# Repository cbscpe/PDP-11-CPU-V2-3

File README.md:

# CPU Board for the PDP-11/Hack V2-3

## Introduction

The PDP-11/Hack is a home-brew PDP-11 compatible computer using eurocard sized
PCBs and DIN41612 bus connectors. The PDP-11/Hack uses it's own bus, named QBUS64,
which is heavily based on the real Q-BUS regarding timing and signalling. The major
difference is that the address/data bus uses non-inverted tri-state signal.

## CPU Card

After the first and so far only CPU card built in 2017 various ideas existed for a
new CPU card that fixes all the issues of the first CPU card and added additional
functions. Most notably the new CPU card has the following features

- DCJ11 processor running up to 22MHz
- 2 or 4 Mbyte of RAM, a PDP-11 can have a maximum of 4Mbyte
- power-up configuration with all 16 bits valid
- maintenance register with all 16 bits valid
- BootROM at the standard IO page addresses 173xxx<sub>8</sub> and 165xxx<sub>8</sub>
- Console using a DC319
- Additional SLU using a second DC319
- Line-time clock
- PDP-11/93,94 compatible advanced status register to read and write the DS1315 real-time clock

## Schematic

## Additional Information

For a full description of this and other projects related not only to PDP-11 
see my [Home Page](https://www.5volts.ch/). For a detailed description of the
CPU Card Version 2-3 see [PDP-11/Hack](https://www.5volts.ch/pages/pdp11hack/)

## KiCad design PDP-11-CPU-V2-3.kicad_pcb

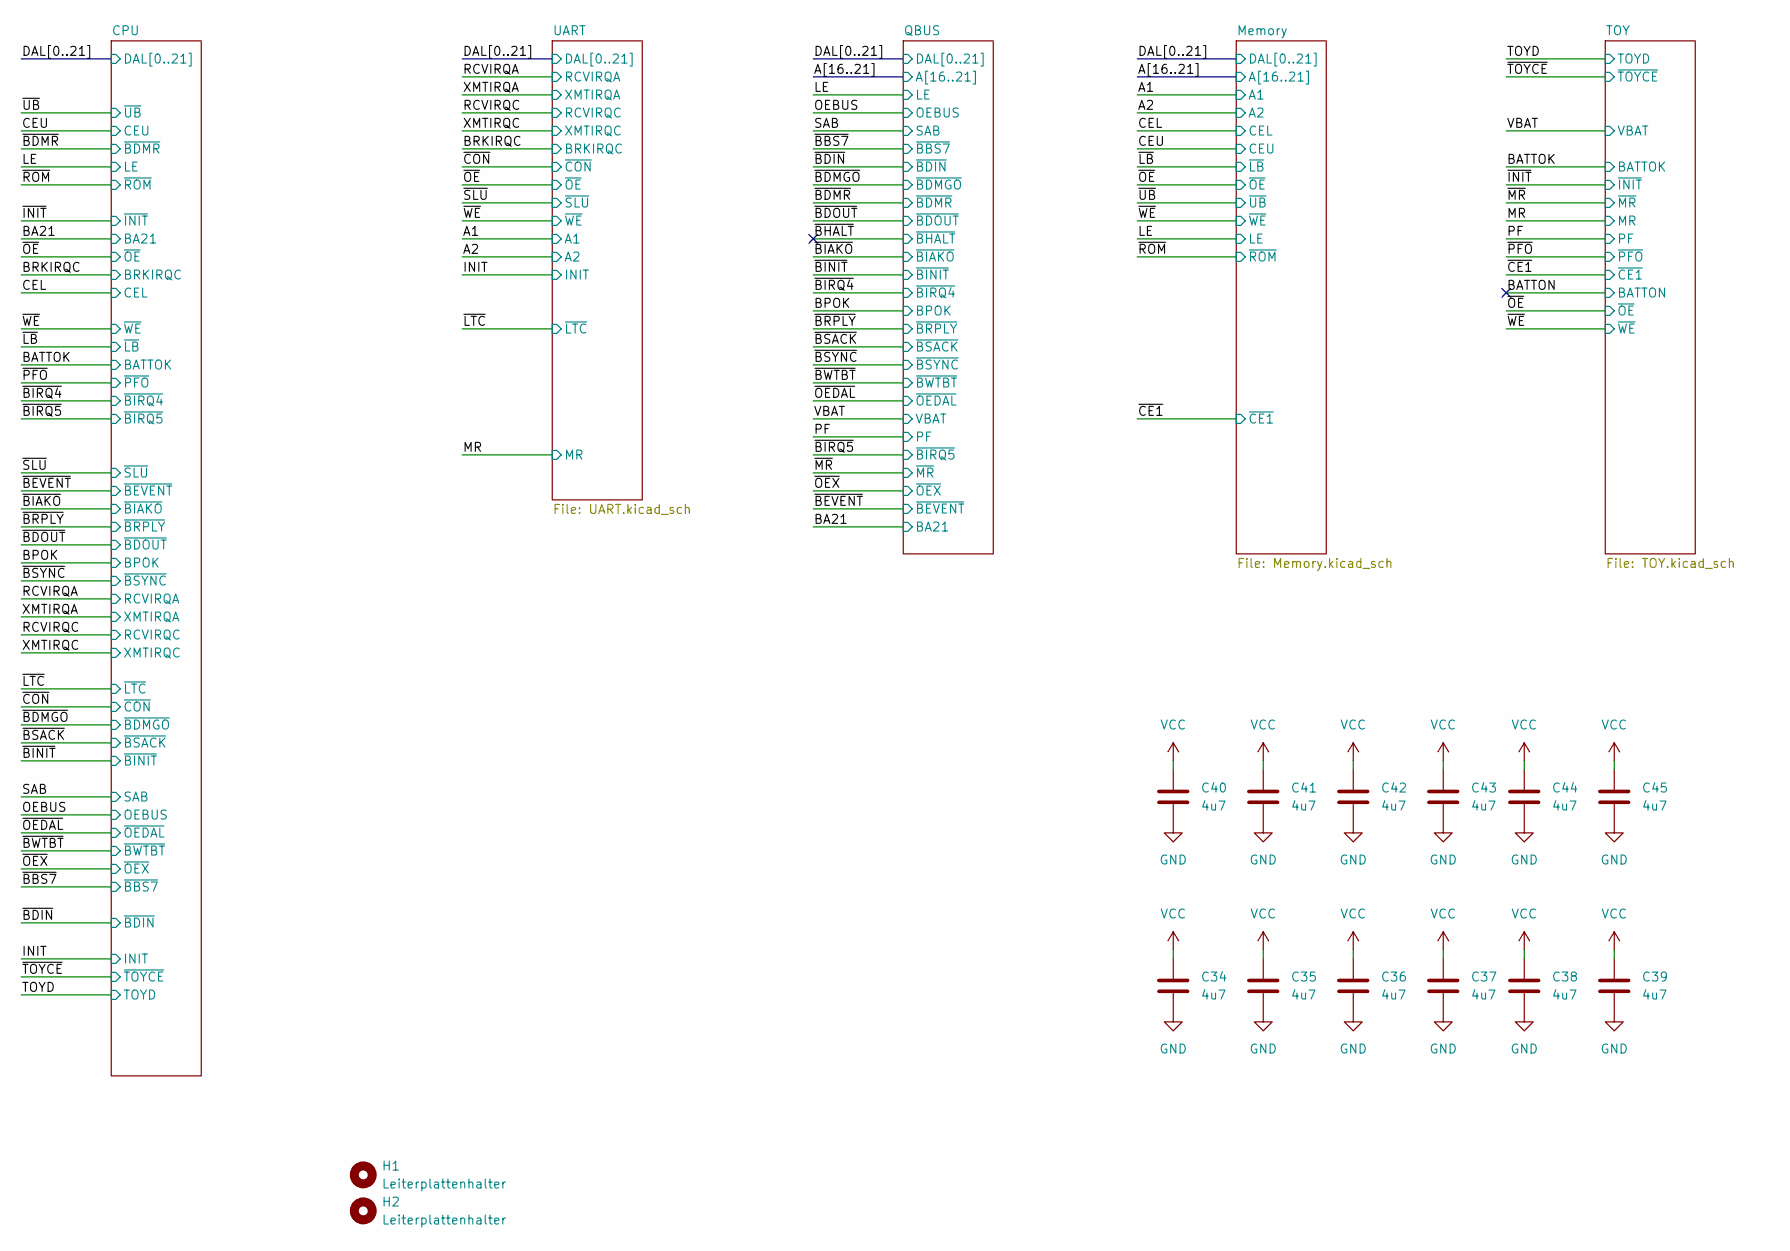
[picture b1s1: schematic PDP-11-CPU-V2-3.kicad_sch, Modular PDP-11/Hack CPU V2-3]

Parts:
C34, C35, C36, C37, C38, C39, C40, C41, C42, C43, C44, C45: 4u7; CP_EIA-3528-12_Kemet-T_HandSolder
H1, H2: Leiterplattenhalter; MountingHole_2.7mm_M2.5_DIN965

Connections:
GND: C34.2, C35.2, C36.2, C37.2, C38.2, C39.2, C40.2, C41.2, C42.2, C43.2, C44.2, C45.2; also elsewhere on the board
VCC: C34.1, C35.1, C36.1, C37.1, C38.1, C39.1, C40.1, C41.1, C42.1, C43.1, C44.1, C45.1; also elsewhere on the board

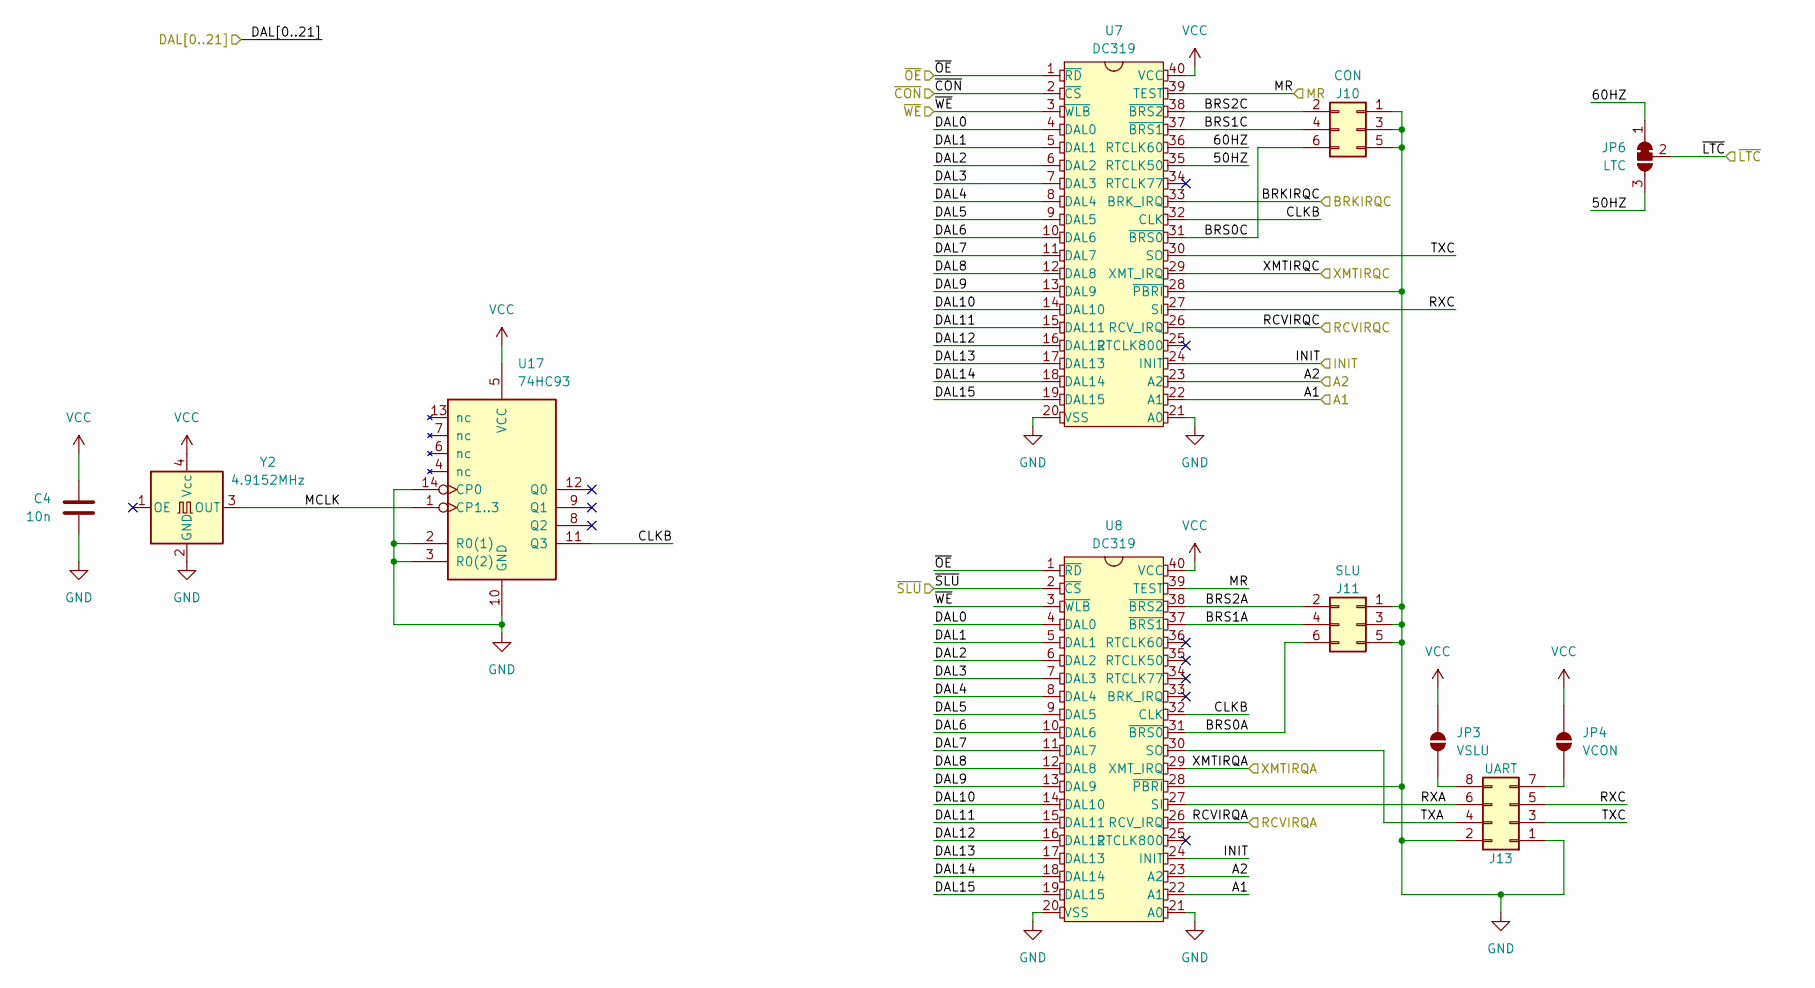
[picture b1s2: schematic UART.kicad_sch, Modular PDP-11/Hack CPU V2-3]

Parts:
C4: 10n; C_0603_1608Metric_Pad1.08x0.95mm_HandSolder
J10: CON; PinHeader_2x03_P2.54mm_Vertical
J11: SLU; PinHeader_2x03_P2.54mm_Vertical
J13: UART; PinHeader_2x04_P2.54mm_Horizontal
JP3: VSLU; SolderJumper-2_P1.3mm_Open_RoundedPad1.0x1.5mm
JP4: VCON; SolderJumper-2_P1.3mm_Open_RoundedPad1.0x1.5mm
JP6: LTC; SolderJumper-3_P1.3mm_Bridged12_RoundedPad1.0x1.5mm
U7, U8: DC319; DIP-40_W15.24mm_Socket
U17: 74HC93; SO-14_3.9x8.65mm_P1.27mm
Y2: 4.9152MHz; Oscillator_SMD_SeikoEpson_SG8002LB-4Pin_5.0x3.2mm_HandSolde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

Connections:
/A1: U7.22 (A1), U8.22 (A1); also elsewhere on the board
/A2: U7.23 (A2), U8.23 (A2); also elsewhere on the board
/BRKIRQC: U7.33 (BRK_IRQ); also elsewhere on the board
/DAL0: U7.4 (DAL0), U8.4 (DAL0); also elsewhere on the board
/DAL1: U7.5 (DAL1), U8.5 (DAL1); also elsewhere on the board
/DAL2: U7.6 (DAL2), U8.6 (DAL2); also elsewhere on the board
/DAL3: U7.7 (DAL3), U8.7 (DAL3); also elsewhere on the board
/DAL4: U7.8 (DAL4), U8.8 (DAL4); also elsewhere on the board
/DAL5: U7.9 (DAL5), U8.9 (DAL5); also elsewhere on the board
/DAL6: U7.10 (DAL6), U8.10 (DAL6); also elsewhere on the board
/DAL7: U7.11 (DAL7), U8.11 (DAL7); also elsewhere on the board
/DAL8: U7.12 (DAL8), U8.12 (DAL8); also elsewhere on the board
/DAL9: U7.13 (DAL9), U8.13 (DAL9); also elsewhere on the board
/DAL10: U7.14 (DAL10), U8.14 (DAL10); also elsewhere on the board
/DAL11: U7.15 (DAL11), U8.15 (DAL11); also elsewhere on the board
/DAL12: U7.16 (DAL12), U8.16 (DAL12); also elsewhere on the board
/DAL13: U7.17 (DAL13), U8.17 (DAL13); also elsewhere on the board
/DAL14: U7.18 (DAL14), U8.18 (DAL14); also elsewhere on the board
/DAL15: U7.19 (DAL15), U8.19 (DAL15); also elsewhere on the board
/INIT: U7.24 (INIT), U8.24 (INIT); also elsewhere on the board
/MR: U7.39 (TEST), U8.39 (TEST); also elsewhere on the board
/RCVIRQA: U8.26 (RCV_IRQ); also elsewhere on the board
/RCVIRQC: U7.26 (RCV_IRQ); also elsewhere on the board
/UART/50HZ: JP6.3 (B), U7.35 (RTCLK50)
/UART/60HZ: JP6.1 (A), U7.36 (RTCLK60)
/UART/BRS0A: J11.6, U8.31 (~BRS0)
/UART/BRS0C: J10.6, U7.31 (~BRS0)
/UART/BRS1A: J11.4, U8.37 (~BRS1)
/UART/BRS1C: J10.4, U7.37 (~BRS1)
/UART/BRS2A: J11.2, U8.38 (~BRS2)
/UART/BRS2C: J10.2, U7.38 (~BRS2)
/UART/CLKB: U7.32 (CLK), U8.32 (CLK), U17.11 (Q3)
/UART/MCLK: U17.1 (CP1..3), Y2.3 (OUT)
/UART/RXA: J13.6, U8.27 (SI)
/UART/RXC: J13.5, U7.27 (SI)
/UART/TXA: J13.4, U8.30 (SO)
/UART/TXC: J13.3, U7.30 (SO)
/XMTIRQA: U8.29 (XMT_IRQ); also elsewhere on the board
/XMTIRQC: U7.29 (XMT_IRQ); also elsewhere on the board
/~CON: U7.2 (~CS); also elsewhere on the board
/~LTC: JP6.2 (C); also elsewhere on the board
/~OE: U7.1 (~RD), U8.1 (~RD); also elsewhere on the board
/~SLU: U8.2 (~CS); also elsewhere on the board
/~WE: U7.3 (~WLB), U8.3 (~WLB); also elsewhere on the board
GND: C4.2, J10.1, J10.3, J10.5, J11.1, J11.3, J11.5, J13.1, J13.2, U7.20 (VSS), U7.21 (A0), U7.28 (~PBRI), U8.20 (VSS), U8.21 (A0), U8.28 (~PBRI), U17.2 (R0(1)), U17.3 (R0(2)), U17.10 (GND), U17.14 (CP0), Y2.2 (GND); also elsewhere on the board
unnamed: J13.7, JP4.1 (A)
unnamed: J13.8, JP3.1 (A)
VCC: C4.1, JP3.2 (B), JP4.2 (B), U7.40 (VCC), U8.40 (VCC), U17.5 (VCC), Y2.4 (Vcc); also elsewhere on the board

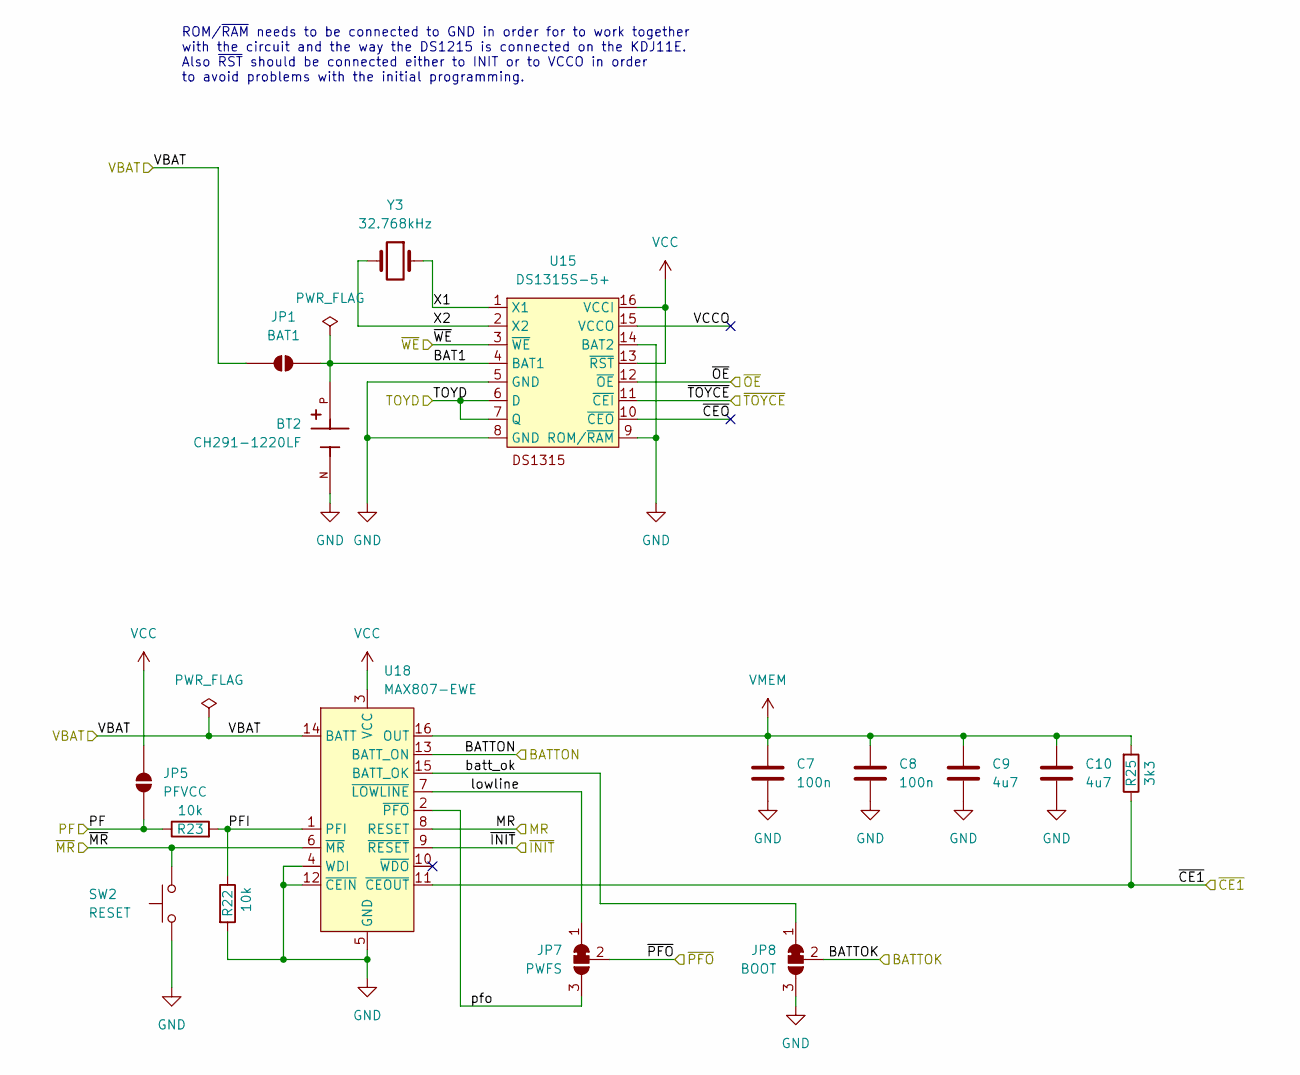
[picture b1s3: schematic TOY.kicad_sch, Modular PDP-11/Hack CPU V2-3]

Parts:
BT2: CH291-1220LF; BAT_CH291-1220LF
C7, C8: 100n; C_0603_1608Metric_Pad1.08x0.95mm_HandSolder
C9, C10: 4u7; CP_EIA-3528-12_Kemet-T_HandSolder
JP1: BAT1; SolderJumper-2_P1.3mm_Open_RoundedPad1.0x1.5mm
JP5: PFVCC; SolderJumper-2_P1.3mm_Open_RoundedPad1.0x1.5mm
JP7: PWFS; SolderJumper-3_P1.3mm_Bridged12_RoundedPad1.0x1.5mm
JP8: BOOT; SolderJumper-3_P1.3mm_Bridged12_RoundedPad1.0x1.5mm
R22, R23: 10k; R_0603_1608Metric_Pad0.98x0.95mm_HandSolder
R25: 3k3; R_0603_1608Metric_Pad0.98x0.95mm_HandSolder
SW2: RESET; SW_PUSH_6mm
U15: DS1315S-5+; SOIC-16W_7.5x10.3mm_P1.27mm
U18: MAX807-EWE; SOIC-16W_7.5x10.3mm_P1.27mm
Y3: 32.768kHz; Crystal_SMD_EuroQuartz_EQ161-2Pin_3.2x1.5mm_HandSoldering

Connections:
/BATTOK: JP8.2 (C); also elsewhere on the board
/BATTON: U18.13 (BATT_ON)
/MR: U18.8 (RESET); also elsewhere on the board
/PF: JP5.2 (B), R23.1; also elsewhere on the board
/TOY/BAT1: BT2.P, JP1.1 (A), U15.4 (BAT1)
/TOY/PFI: R22.1, R23.2, U18.1 (PFI)
/TOY/VCCO: U15.15 (VCCO)
/TOY/X1: U15.1 (X1), Y3.1
/TOY/X2: U15.2 (X2), Y3.2
/TOY/batt_ok: JP8.1 (A), U18.15 (BATT_OK)
/TOY/lowline: JP7.1 (A), U18.7 (~LOWLINE)
/TOY/pfo: JP7.3 (B), U18.2 (~PFO)
/TOY/~CEO: U15.10 (~CEO)
/TOYD: U15.6 (D), U15.7 (Q); also elsewhere on the board
/VBAT: JP1.2 (B), U18.14 (BATT); also elsewhere on the board
/~CE1: R25.1, U18.11 (~CEOUT); also elsewhere on the board
/~INIT: U18.9 (~RESET); also elsewhere on the board
/~MR: SW2.2, U18.6 (~MR); also elsewhere on the board
/~OE: U15.12 (~OE); also elsewhere on the board
/~PFO: JP7.2 (C); also elsewhere on the board
/~TOYCE: U15.11 (~CEI); also elsewhere on the board
/~WE: U15.3 (~WE); also elsewhere on the board
GND: BT2.N, C7.2, C8.2, C9.2, C10.2, JP8.3 (B), R22.2, SW2.1, U15.5 (GND), U15.8 (GND), U15.9 (ROM/~RAM), U15.14 (BAT2), U18.4 (WDI), U18.5 (GND), U18.12 (~CEIN); also elsewhere on the board
VCC: JP5.1 (A), U15.13 (~RST), U15.16 (VCCI), U18.3 (VCC); also elsewhere on the board
VMEM: C7.1, C8.1, C9.1, C10.1, R25.2, U18.16 (OUT); also elsewhere on the board

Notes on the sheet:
ROM/~{RAM} needs to be connected to GND in order for to work together with the circuit and the way the DS1215 is connected on the KDJ11E. Also ~{RST} should be connected either to INIT or to VCCO in order to avoid problems with the initial programming.

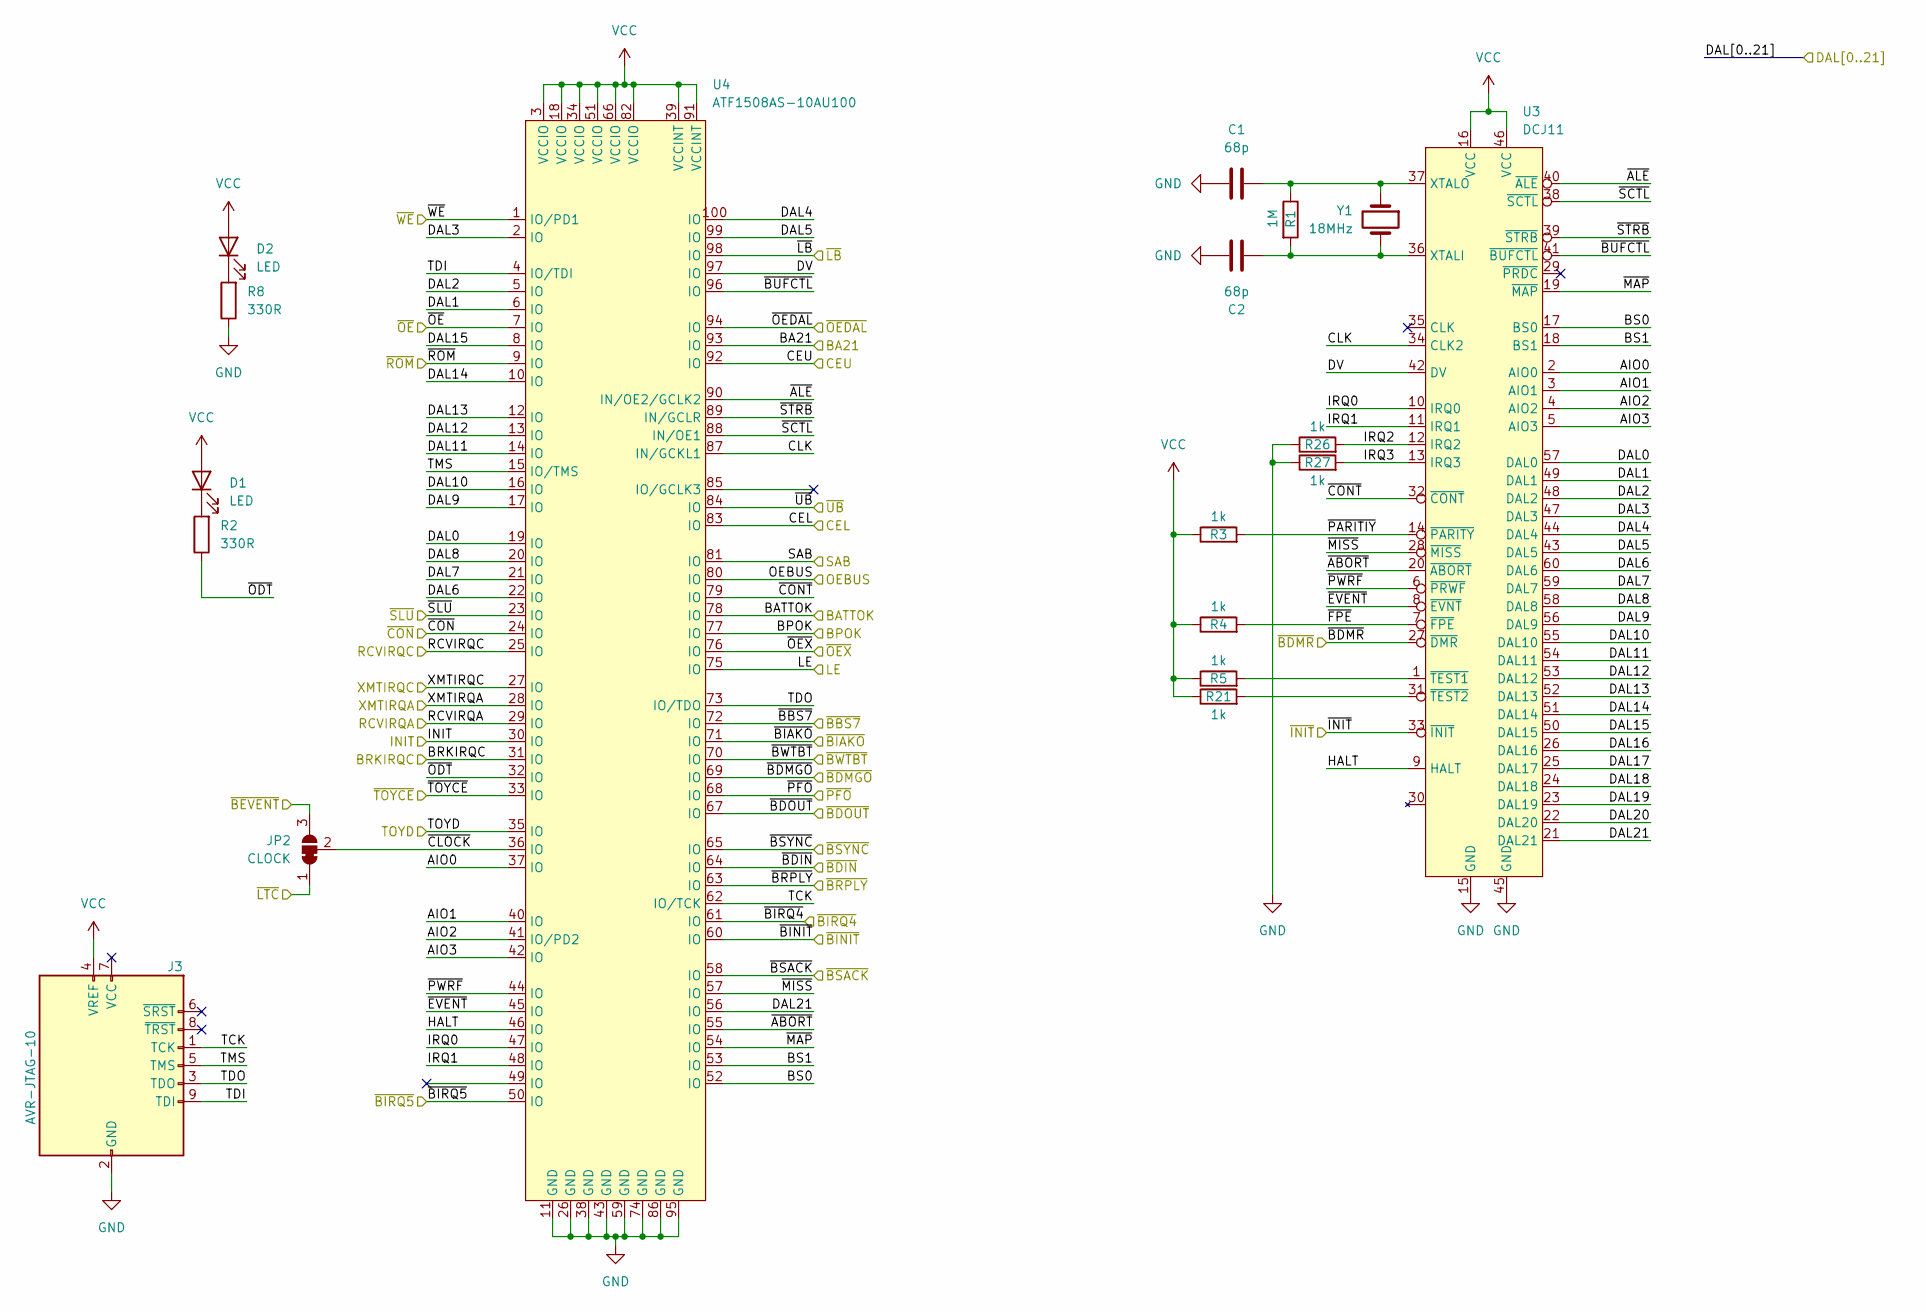
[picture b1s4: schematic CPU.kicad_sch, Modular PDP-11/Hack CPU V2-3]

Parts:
C1, C2: 68p; C_0603_1608Metric_Pad1.08x0.95mm_HandSolder
D1, D2: LED; LED_1206_3216Metric_Pad1.42x1.75mm_HandSolder
J3: AVR-JTAG-10; IDC-Header_2x05_P2.54mm_Horizontal
JP2: CLOCK; SolderJumper-3_P1.3mm_Bridged12_RoundedPad1.0x1.5mm
R1: 1M; R_0603_1608Metric_Pad0.98x0.95mm_HandSolder
R2, R8: 330R; R_0603_1608Metric_Pad0.98x0.95mm_HandSolder
R3, R4, R5, R21, R26, R27: 1k; R_0603_1608Metric_Pad0.98x0.95mm_HandSolder
U3: DCJ11; DIP-60_1300
U4: ATF1508AS-10AU100; TQFP-100_14x14mm_P0.5mm
Y1: 18MHz; Crystal_SMD_5032-2Pin_5.0x3.2mm_HandSoldering

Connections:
/BA21: U4.93 (IO); also elsewhere on the board
/BATTOK: U4.78 (IO); also elsewhere on the board
/BPOK: U4.77 (IO); also elsewhere on the board
/BRKIRQC: U4.31 (IO); also elsewhere on the board
/CEL: U4.83 (IO); also elsewhere on the board
/CEU: U4.92 (IO); also elsewhere on the board
/CPU/AIO0: U3.2 (AIO0), U4.37 (IO)
/CPU/AIO1: U3.3 (AIO1), U4.40 (IO)
/CPU/AIO2: U3.4 (AIO2), U4.41 (IO/PD2)
/CPU/AIO3: U3.5 (AIO3), U4.42 (IO)
/CPU/BS0: U3.17 (BS0), U4.52 (IO)
/CPU/BS1: U3.18 (BS1), U4.53 (IO)
/CPU/CLK: U3.34 (CLK2), U4.87 (IN/GCKL1)
/CPU/DV: U3.42 (DV), U4.97 (IO)
/CPU/HALT: U3.9 (HALT), U4.46 (IO)
/CPU/IRQ0: U3.10 (IRQ0), U4.47 (IO)
/CPU/IRQ1: U3.11 (IRQ1), U4.48 (IO)
/CPU/IRQ2: R26.2, U3.12 (IRQ2)
/CPU/IRQ3: R27.2, U3.13 (IRQ3)
/CPU/TCK: J3.1 (TCK), U4.62 (IO/TCK)
/CPU/TDI: J3.9 (TDI), U4.4 (IO/TDI)
/CPU/TDO: J3.3 (TDO), U4.73 (IO/TDO)
/CPU/TMS: J3.5 (TMS), U4.15 (IO/TMS)
/CPU/~ABORT: U3.20 (~ABORT), U4.55 (IO)
/CPU/~ALE: U3.40 (~ALE), U4.90 (IN/OE2/GCLK2)
/CPU/~BUFCTL: U3.41 (~BUFCTL), U4.96 (IO)
/CPU/~CLOCK: JP2.2 (C), U4.36 (IO)
/CPU/~CONT: U3.32 (~CONT), U4.79 (IO)
/CPU/~EVENT: U3.8 (~EVNT), U4.45 (IO)
/CPU/~FPE: R4.2, U3.7 (~FPE)
/CPU/~MAP: U3.19 (~MAP), U4.54 (IO)
/CPU/~MISS: U3.28 (~MISS), U4.57 (IO)
/CPU/~ODT: R2.1, U4.32 (IO)
/CPU/~PARITIY: R3.2, U3.14 (~PARITY)
/CPU/~PWRF: U3.6 (~PRWF), U4.44 (IO)
/CPU/~SCTL: U3.38 (~SCTL), U4.88 (IN/OE1)
/CPU/~STRB: U3.39 (~STRB), U4.89 (IN/GCLR)
/DAL0: U3.57 (DAL0), U4.19 (IO); also elsewhere on the board
/DAL1: U3.49 (DAL1), U4.6 (IO); also elsewhere on the board
/DAL2: U3.48 (DAL2), U4.5 (IO); also elsewhere on the board
/DAL3: U3.47 (DAL3), U4.2 (IO); also elsewhere on the board
/DAL4: U3.44 (DAL4), U4.100 (IO); also elsewhere on the board
/DAL5: U3.43 (DAL5), U4.99 (IO); also elsewhere on the board
/DAL6: U3.60 (DAL6), U4.22 (IO); also elsewhere on the board
/DAL7: U3.59 (DAL7), U4.21 (IO); also elsewhere on the board
/DAL8: U3.58 (DAL8), U4.20 (IO); also elsewhere on the board
/DAL9: U3.56 (DAL9), U4.17 (IO); also elsewhere on the board
/DAL10: U3.55 (DAL10), U4.16 (IO); also elsewhere on the board
/DAL11: U3.54 (DAL11), U4.14 (IO); also elsewhere on the board
/DAL12: U3.53 (DAL12), U4.13 (IO); also elsewhere on the board
/DAL13: U3.52 (DAL13), U4.12 (IO); also elsewhere on the board
/DAL14: U3.51 (DAL14), U4.10 (IO); also elsewhere on the board
/DAL15: U3.50 (DAL15), U4.8 (IO); also elsewhere on the board
/DAL16: U3.26 (DAL16); also elsewhere on the board
/DAL17: U3.25 (DAL17); also elsewhere on the board
/DAL18: U3.24 (DAL18); also elsewhere on the board
/DAL19: U3.23 (DAL19); also elsewhere on the board
/DAL20: U3.22 (DAL20); also elsewhere on the board
/DAL21: U3.21 (DAL21), U4.56 (IO)
/INIT: U4.30 (IO); also elsewhere on the board
/LE: U4.75 (IO); also elsewhere on the board
/OEBUS: U4.80 (IO); also elsewhere on the board
/RCVIRQA: U4.29 (IO); also elsewhere on the board
/RCVIRQC: U4.25 (IO); also elsewhere on the board
/SAB: U4.81 (IO); also elsewhere on the board
/TOYD: U4.35 (IO); also elsewhere on the board
/XMTIRQA: U4.28 (IO); also elsewhere on the board
/XMTIRQC: U4.27 (IO); also elsewhere on the board
/~BBS7: U4.72 (IO); also elsewhere on the board
/~BDIN: U4.64 (IO); also elsewhere on the board
/~BDMGO: U4.69 (IO); also elsewhere on the board
/~BDMR: U3.27 (~DMR); also elsewhere on the board
/~BDOUT: U4.67 (IO); also elsewhere on the board
/~BEVENT: JP2.3 (B); also elsewhere on the board
/~BIAKO: U4.71 (IO); also elsewhere on the board
/~BINIT: U4.60 (IO); also elsewhere on the board
/~BIRQ4: U4.61 (IO); also elsewhere on the board
/~BIRQ5: U4.50 (IO); also elsewhere on the board
/~BRPLY: U4.63 (IO); also elsewhere on the board
/~BSACK: U4.58 (IO); also elsewhere on the board
/~BSYNC: U4.65 (IO); also elsewhere on the board
/~BWTBT: U4.70 (IO); also elsewhere on the board
/~CON: U4.24 (IO); also elsewhere on the board
/~INIT: U3.33 (~INIT); also elsewhere on the board
/~LB: U4.98 (IO); also elsewhere on the board
/~LTC: JP2.1 (A); also elsewhere on the board
/~OEDAL: U4.94 (IO); also elsewhere on the board
/~OEX: U4.76 (IO); also elsewhere on the board
/~OE: U4.7 (IO); also elsewhere on the board
/~PFO: U4.68 (IO); also elsewhere on the board
/~ROM: U4.9 (IO); also elsewhere on the board
/~SLU: U4.23 (IO); also elsewhere on the board
/~TOYCE: U4.33 (IO); also elsewhere on the board
/~UB: U4.84 (IO); also elsewhere on the board
/~WE: U4.1 (IO/PD1); also elsewhere on the board
GND: C1.1, C2.1, J3.2 (GND), J3.10 (GND), R8.1, R26.1, R27.1, U3.15 (GND), U3.45 (GND), U4.11 (GND), U4.26 (GND), U4.38 (GND), U4.43 (GND), U4.59 (GND), U4.74 (GND), U4.86 (GND), U4.95 (GND); also elsewhere on the board
unnamed: D1.1 (K), R2.2
unnamed: D2.1 (K), R8.2
unnamed: C2.2, R1.2, U3.36 (XTALI), Y1.2
unnamed: C1.2, R1.1, U3.37 (XTALO), Y1.1
unnamed: R5.2, U3.1 (~TEST1)
unnamed: R21.2, U3.31 (~TEST2)
VCC: D1.2 (A), D2.2 (A), J3.4 (VREF), R3.1, R4.1, R5.1, R21.1, U3.16 (VCC), U3.46 (VCC), U4.3 (VCCIO), U4.18 (VCCIO), U4.34 (VCCIO), U4.39 (VCCINT), U4.51 (VCCIO), U4.66 (VCCIO), U4.82 (VCCIO), U4.91 (VCCINT); also elsewhere on the board

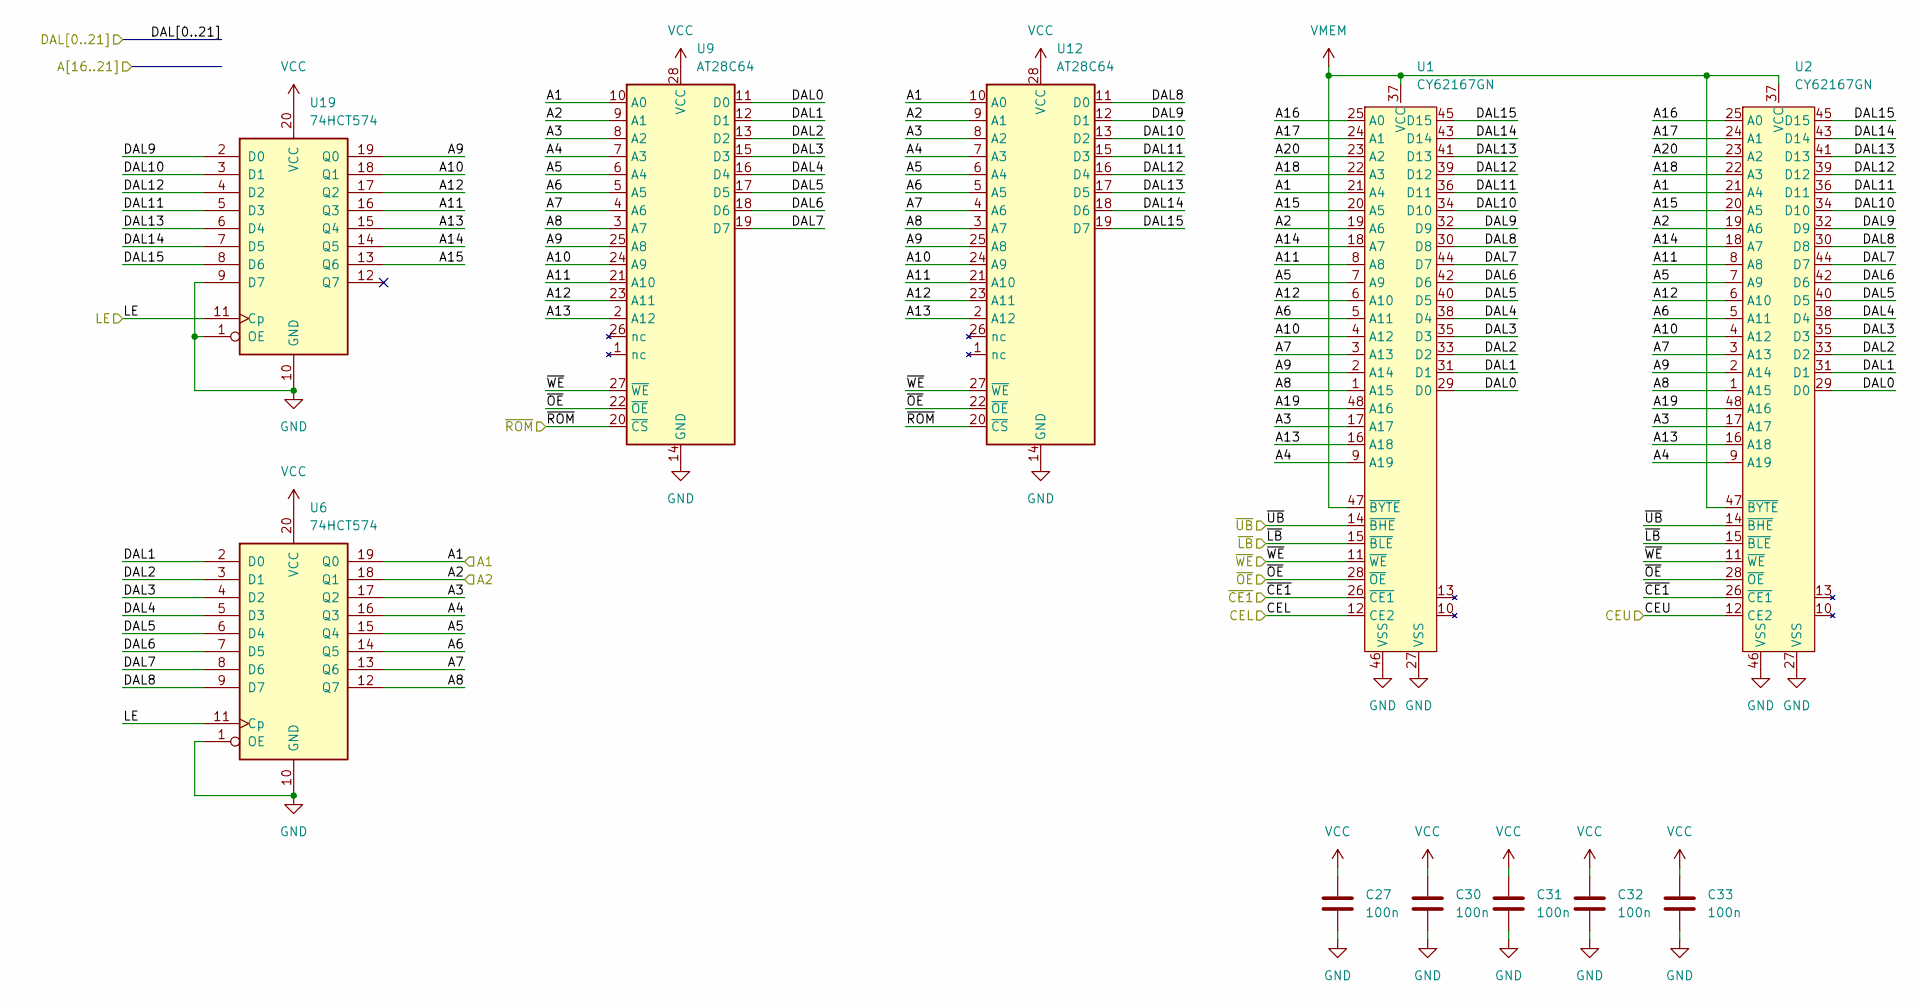
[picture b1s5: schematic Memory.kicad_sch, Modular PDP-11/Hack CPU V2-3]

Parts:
C27, C30, C31, C32, C33: 100n; C_0603_1608Metric_Pad1.08x0.95mm_HandSolder
U1, U2: CY62167GN; TSOP-I-48_18.4x12mm_P0.5mm
U6, U19: 74HCT574; TSSOP-20_4.4x6.5mm_P0.65mm
U9, U12: AT28C64; SOIC-28W_7.5x17.9mm_P1.27mm

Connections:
/A1: U1.21 (A4), U2.21 (A4), U6.19 (Q0), U9.10 (A0), U12.10 (A0); also elsewhere on the board
/A2: U1.19 (A6), U2.19 (A6), U6.18 (Q1), U9.9 (A1), U12.9 (A1); also elsewhere on the board
/A16: U1.25 (A0), U2.25 (A0); also elsewhere on the board
/A17: U1.24 (A1), U2.24 (A1); also elsewhere on the board
/A18: U1.22 (A3), U2.22 (A3); also elsewhere on the board
/A19: U1.48 (A16), U2.48 (A16); also elsewhere on the board
/A20: U1.23 (A2), U2.23 (A2); also elsewhere on the board
/CEL: U1.12 (CE2); also elsewhere on the board
/CEU: U2.12 (CE2); also elsewhere on the board
/DAL0: U1.29 (D0), U2.29 (D0), U9.11 (D0); also elsewhere on the board
/DAL1: U1.31 (D1), U2.31 (D1), U6.2 (D0), U9.12 (D1); also elsewhere on the board
/DAL2: U1.33 (D2), U2.33 (D2), U6.3 (D1), U9.13 (D2); also elsewhere on the board
/DAL3: U1.35 (D3), U2.35 (D3), U6.4 (D2), U9.15 (D3); also elsewhere on the board
/DAL4: U1.38 (D4), U2.38 (D4), U6.5 (D3), U9.16 (D4); also elsewhere on the board
/DAL5: U1.40 (D5), U2.40 (D5), U6.6 (D4), U9.17 (D5); also elsewhere on the board
/DAL6: U1.42 (D6), U2.42 (D6), U6.7 (D5), U9.18 (D6); also elsewhere on the board
/DAL7: U1.44 (D7), U2.44 (D7), U6.8 (D6), U9.19 (D7); also elsewhere on the board
/DAL8: U1.30 (D8), U2.30 (D8), U6.9 (D7), U12.11 (D0); also elsewhere on the board
/DAL9: U1.32 (D9), U2.32 (D9), U12.12 (D1), U19.2 (D0); also elsewhere on the board
/DAL10: U1.34 (D10), U2.34 (D10), U12.13 (D2), U19.3 (D1); also elsewhere on the board
/DAL11: U1.36 (D11), U2.36 (D11), U12.15 (D3), U19.5 (D3); also elsewhere on the board
/DAL12: U1.39 (D12), U2.39 (D12), U12.16 (D4), U19.4 (D2); also elsewhere on the board
/DAL13: U1.41 (D13), U2.41 (D13), U12.17 (D5), U19.6 (D4); also elsewhere on the board
/DAL14: U1.43 (D14), U2.43 (D14), U12.18 (D6), U19.7 (D5); also elsewhere on the board
/DAL15: U1.45 (D15), U2.45 (D15), U12.19 (D7), U19.8 (D6); also elsewhere on the board
/LE: U6.11 (Cp), U19.11 (Cp); also elsewhere on the board
/Memory/A3: U1.17 (A17), U2.17 (A17), U6.17 (Q2), U9.8 (A2), U12.8 (A2)
/Memory/A4: U1.9 (A19), U2.9 (A19), U6.16 (Q3), U9.7 (A3), U12.7 (A3)
/Memory/A5: U1.7 (A9), U2.7 (A9), U6.15 (Q4), U9.6 (A4), U12.6 (A4)
/Memory/A6: U1.5 (A11), U2.5 (A11), U6.14 (Q5), U9.5 (A5), U12.5 (A5)
/Memory/A7: U1.3 (A13), U2.3 (A13), U6.13 (Q6), U9.4 (A6), U12.4 (A6)
/Memory/A8: U1.1 (A15), U2.1 (A15), U6.12 (Q7), U9.3 (A7), U12.3 (A7)
/Memory/A9: U1.2 (A14), U2.2 (A14), U9.25 (A8), U12.25 (A8), U19.19 (Q0)
/Memory/A10: U1.4 (A12), U2.4 (A12), U9.24 (A9), U12.24 (A9), U19.18 (Q1)
/Memory/A11: U1.8 (A8), U2.8 (A8), U9.21 (A10), U12.21 (A10), U19.16 (Q3)
/Memory/A12: U1.6 (A10), U2.6 (A10), U9.23 (A11), U12.23 (A11), U19.17 (Q2)
/Memory/A13: U1.16 (A18), U2.16 (A18), U9.2 (A12), U12.2 (A12), U19.15 (Q4)
/Memory/A14: U1.18 (A7), U2.18 (A7), U19.14 (Q5)
/Memory/A15: U1.20 (A5), U2.20 (A5), U19.13 (Q6)
/~CE1: U1.26 (~CE1), U2.26 (~CE1); also elsewhere on the board
/~LB: U1.15 (~BLE), U2.15 (~BLE); also elsewhere on the board
/~OE: U1.28 (~OE), U2.28 (~OE), U9.22 (~OE), U12.22 (~OE); also elsewhere on the board
/~ROM: U9.20 (~CS), U12.20 (~CS); also elsewhere on the board
/~UB: U1.14 (~BHE), U2.14 (~BHE); also elsewhere on the board
/~WE: U1.11 (~WE), U2.11 (~WE), U9.27 (~WE), U12.27 (~WE); also elsewhere on the board
GND: C27.2, C30.2, C31.2, C32.2, C33.2, U1.27 (VSS), U1.46 (VSS), U2.27 (VSS), U2.46 (VSS), U6.1 (OE), U6.10 (GND), U9.14 (GND), U12.14 (GND), U19.1 (OE), U19.9 (D7), U19.10 (GND); also elsewhere on the board
VCC: C27.1, C30.1, C31.1, C32.1, C33.1, U6.20 (VCC), U9.28 (VCC), U12.28 (VCC), U19.20 (VCC); also elsewhere on the board
VMEM: U1.37 (VCC), U1.47 (~BYTE), U2.37 (VCC), U2.47 (~BYTE); also elsewhere on the board

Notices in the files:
CPU.kicad_sch:
Copyright Peter Schranz 2026
PDP-11-CPU-V2-3.kicad_pcb:
© Peter Schranz, October 2026
